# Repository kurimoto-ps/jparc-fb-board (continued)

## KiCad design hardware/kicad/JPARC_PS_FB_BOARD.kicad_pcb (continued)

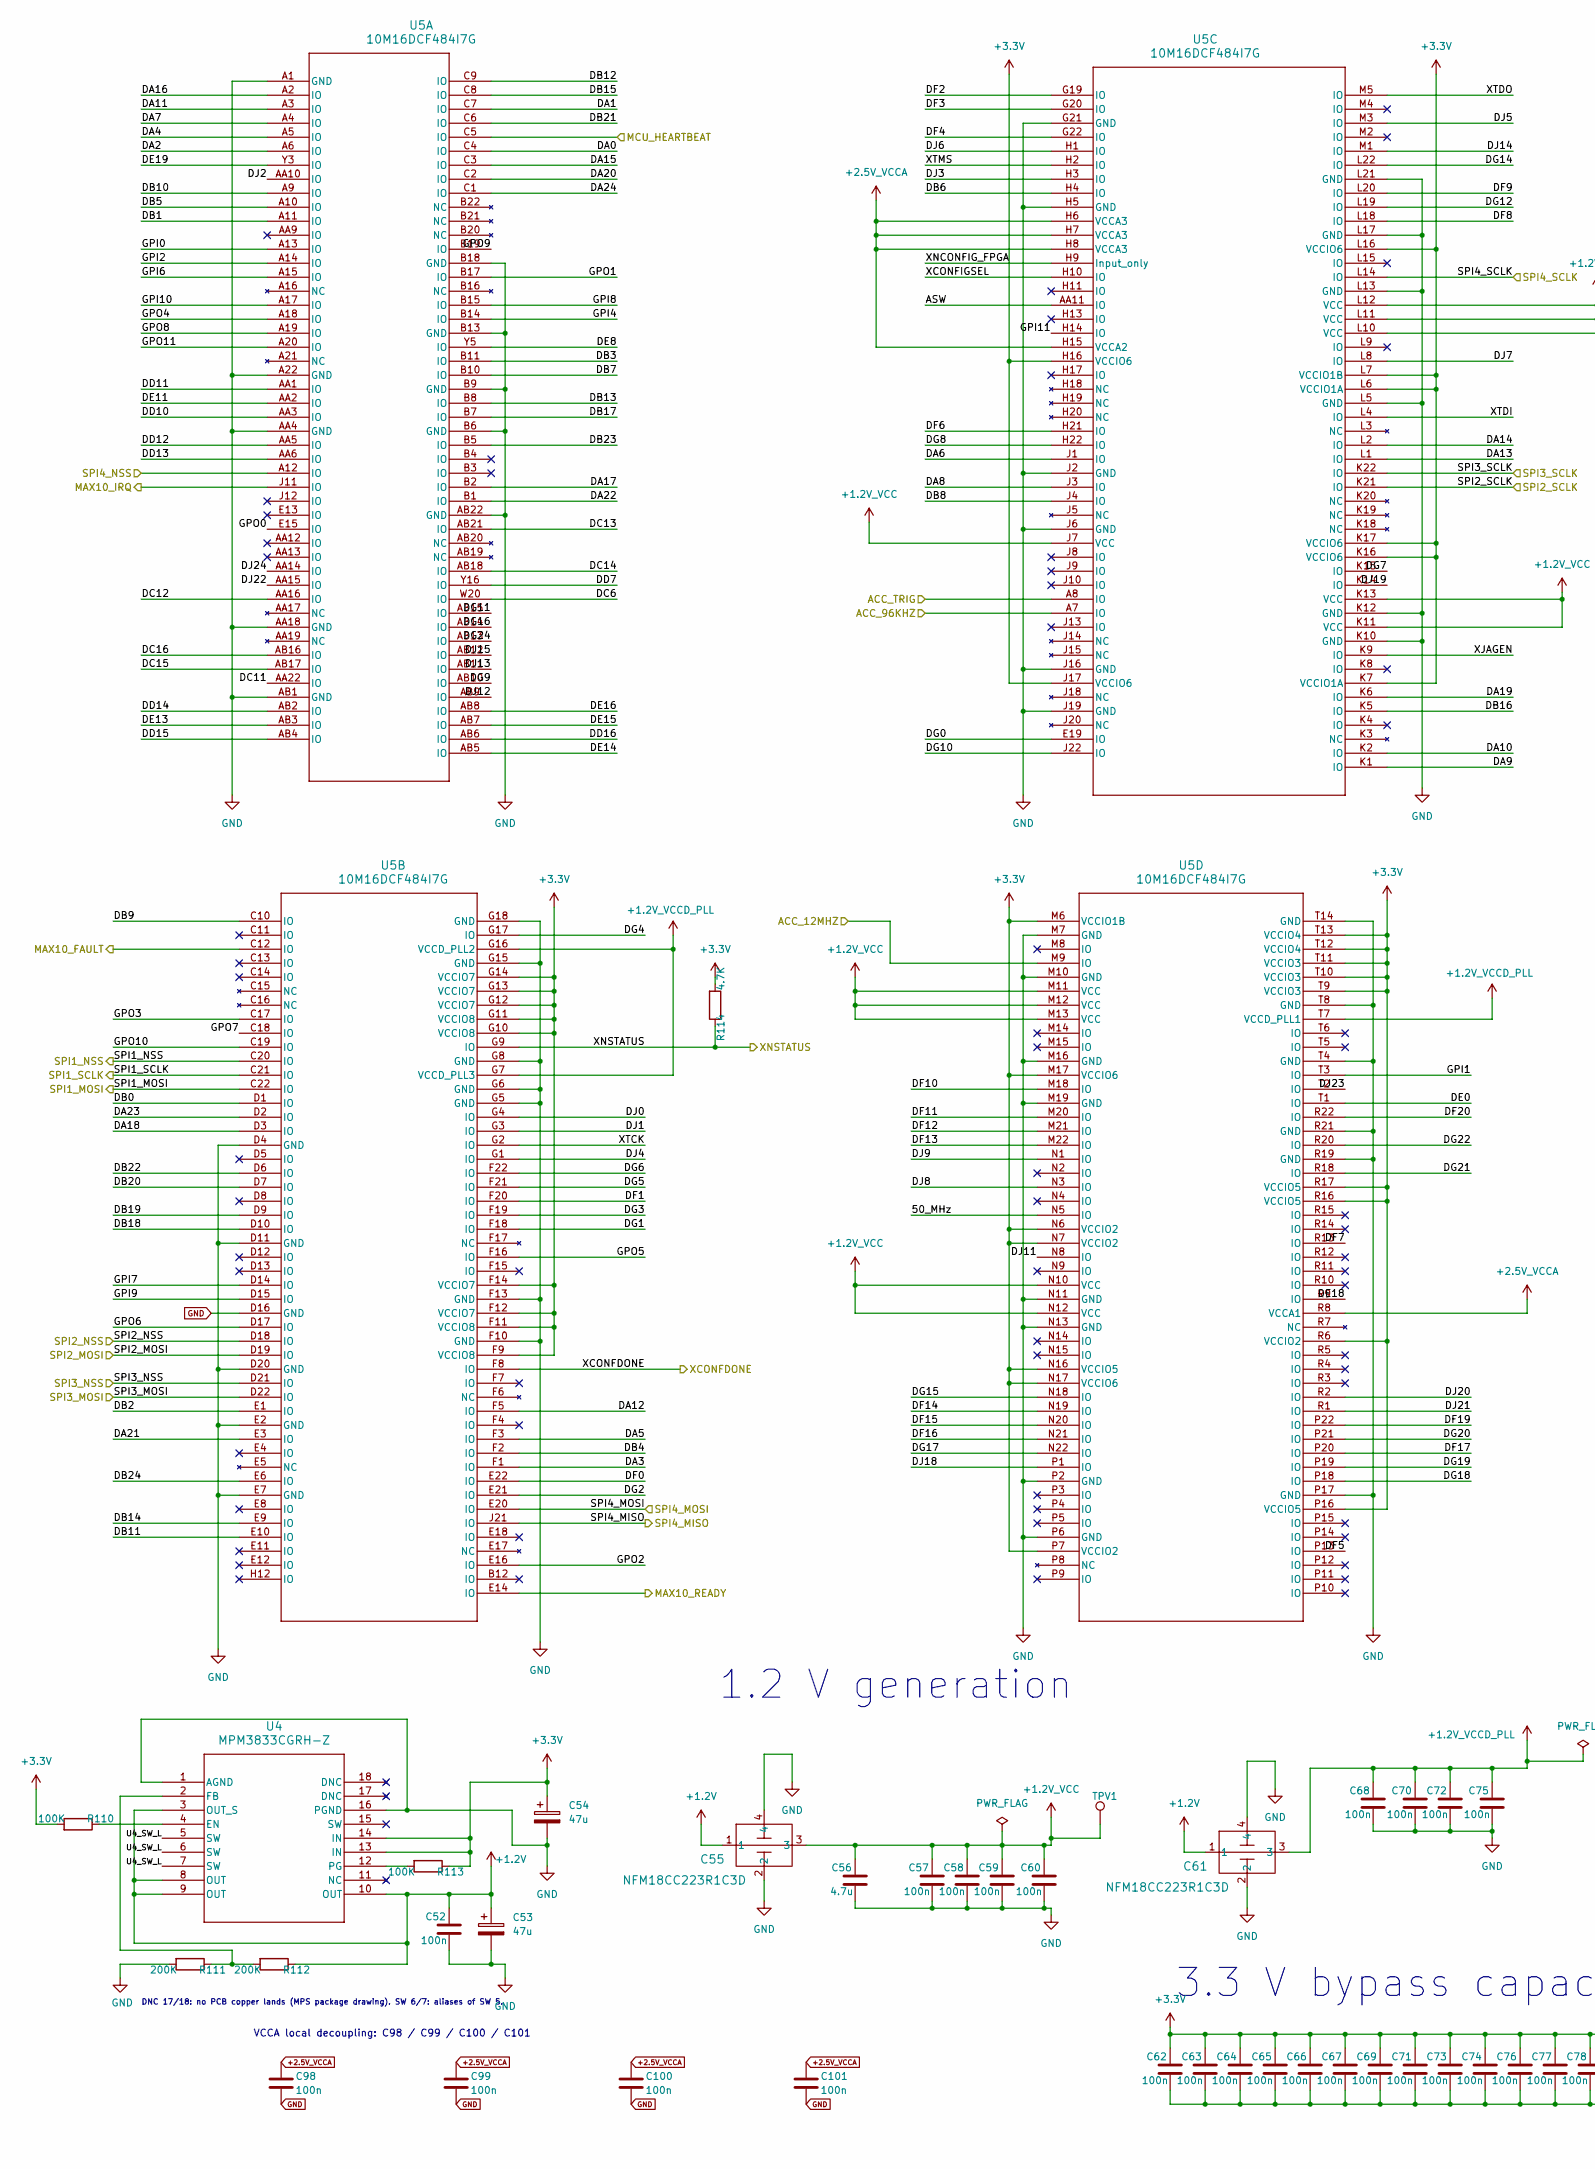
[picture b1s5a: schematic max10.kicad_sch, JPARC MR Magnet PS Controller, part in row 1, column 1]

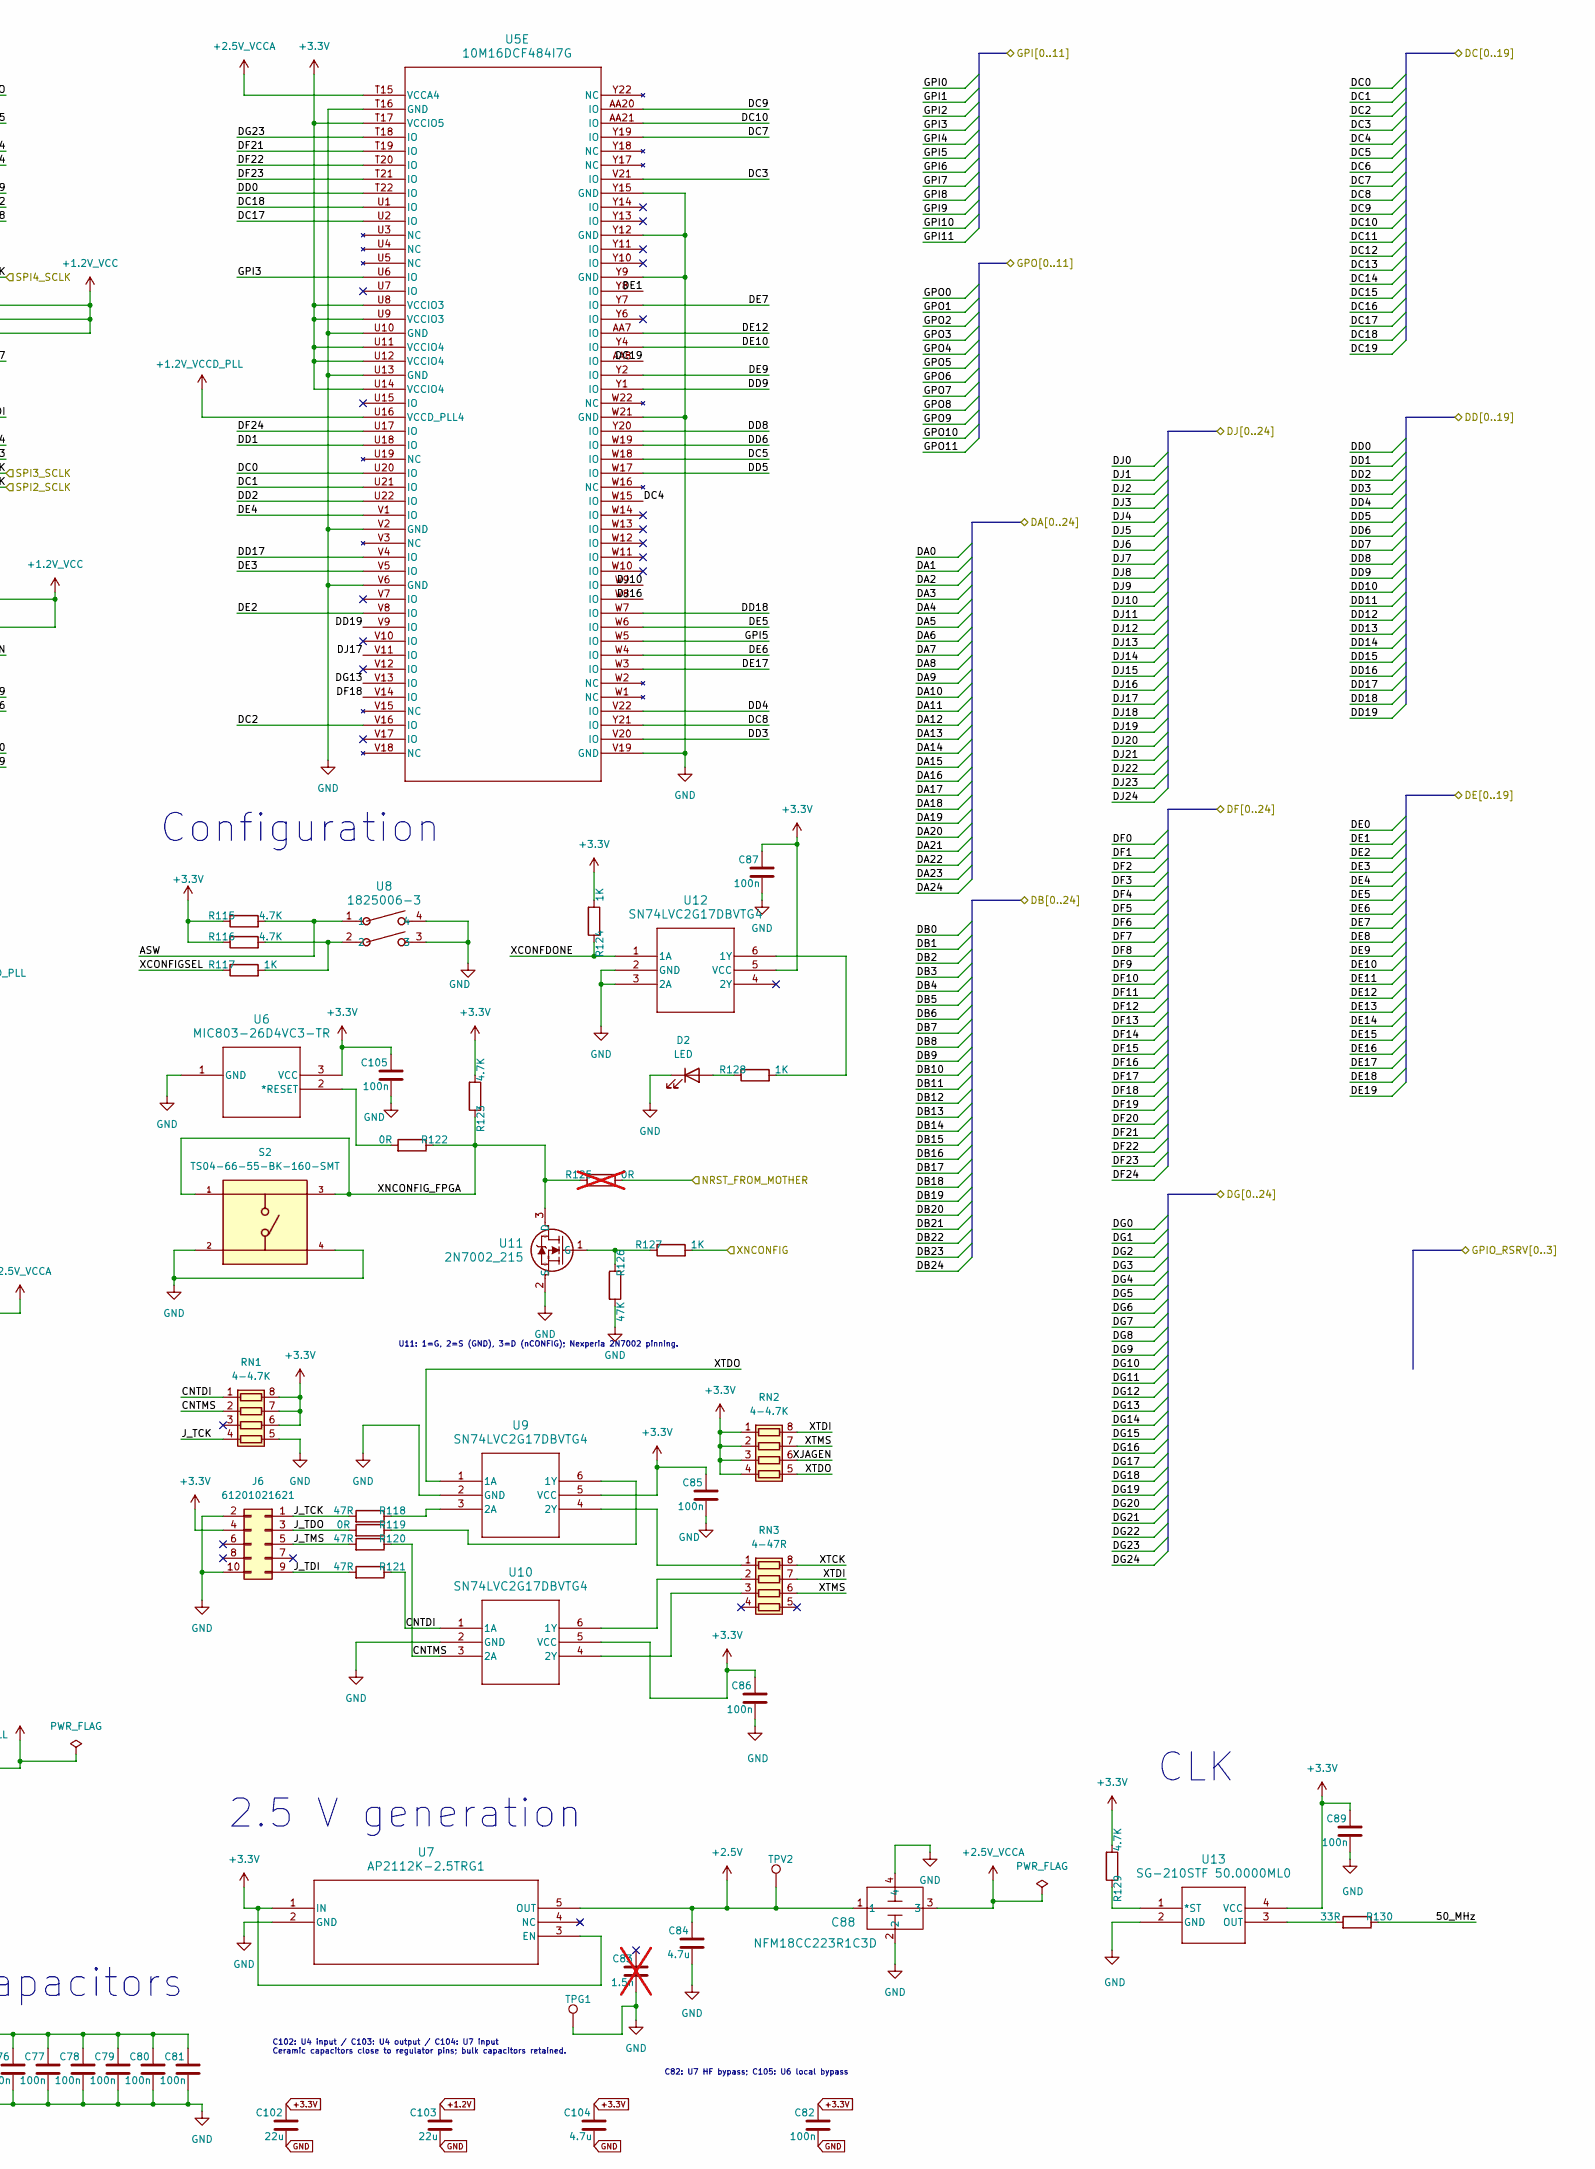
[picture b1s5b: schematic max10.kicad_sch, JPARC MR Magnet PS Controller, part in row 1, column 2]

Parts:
C52, C57, C58, C59, C60, C62, C63, C64, C65, C66, C67, C68, C69, C70, C71, C72, C73, C74, C75, C76, C77, C78, C79, C80, C81, C82, C85, C86, C87, C89, C98, C99, C100, C101, C105: 100n; C_0402_1005Metric
C53, C54: 47u; CP_Elec_5x5.8
C55, C61, C88: NFM18CC223R1C3D; NFM18CC_4Pad_Corrected
C56, C84, C104: 4.7u; C_0805_2012Metric
C83: 1.5n; C_0603_1608Metric; not fitted
C102, C103: 22u; C_0805_2012Metric
D2: LED; LED_0805_2012Metric
J6: 61201021621; IDC-Header_2x05_P2.54mm_Vertical
R110, R113: 100K; R_0603_1608Metric
R111, R112: 200K; R_0603_1608Metric
R114, R115, R116, R123, R129: 4.7K; R_0603_1608Metric
R117, R124, R127, R128: 1K; R_0603_1608Metric
R118, R120, R121: 47R; R_0402_1005Metric
R119, R122: 0R; R_0603_1608Metric
R125: 0R; R_0603_1608Metric; not fitted
R126: 47K; R_0603_1608Metric
R130: 33R; R_0402_1005Metric
RN1, RN2: 4-4.7K; R_Cat16-4
RN3: 4-47R; R_Cat16-4
S2: TS04-66-55-BK-160-SMT; SW_TS04-66-55-BK-160-SMT; PARTREV 1.0
TPG1: TestPoint_THTPad_D1.0mm_Drill0.5mm
TPV1, TPV2: TestPoint_Pad_D1.5mm
U4: MPM3833CGRH-Z; MPM3833C_QFN18_Manufacturer
U5: 10M16DCF484I7G; FBGA484_WIREBOND_A2p40_INT
U6: MIC803-26D4VC3-TR; 21-0075D_MXM
U7: AP2112K-2.5TRG1; UJ_5_ADI
U8: 1825006-3; SWSO4_386X100P100
U9, U10, U12: SN74LVC2G17DBVTG4; DBV6_TEX
U11: 2N7002_215; TO-236AB_NEX
U13: SG-210STF 50.0000ML0; SG-210STF_Epson_Recommended

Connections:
+1.2V: C52.1, C53.1, C55.1, C61.1, C103.1, R112.1, U4.3 (OUT_S), U4.8 (OUT), U4.9 (OUT), U4.10 (OUT)
+1.2V_VCC: C55.3, C56.1, C57.1, C58.1, C59.1, C60.1, TPV1.1 (1_1), U5.J7 (VCC), U5.K11 (VCC), U5.K13 (VCC), U5.L10 (VCC), U5.L11 (VCC), U5.L12 (VCC), U5.M11 (VCC), U5.M12 (VCC), U5.M13 (VCC), U5.N10 (VCC), U5.N12 (VCC)
+1.2V_VCCD_PLL: C61.3, C68.1, C70.1, C72.1, C75.1, U5.G7 (VCCD_PLL3), U5.G16 (VCCD_PLL2), U5.T7 (VCCD_PLL1), U5.U16 (VCCD_PLL4)
+2.5V: C84.1, C88.1, TPV2.1 (1_1), U7.5 (OUT)
+2.5V_VCCA: C88.3, C98.1, C99.1, C100.1, C101.1, U5.H6 (VCCA3), U5.H7 (VCCA3), U5.H8 (VCCA3), U5.H15 (VCCA2), U5.R8 (VCCA1), U5.T15 (VCCA4)
+3.3V: C54.1, C62.1, C63.1, C64.1, C65.1, C66.1, C67.1, C69.1, C71.1, C73.1, C74.1, C76.1, C77.1, C78.1, C79.1, C80.1, C81.1, C82.1, C85.1, C86.1, C87.1, C89.1, C102.1, C104.1, C105.1, J6.4, R110.2, R113.1, R114.2, R115.1, R116.1, R123.2, R124.2, R129.2, RN1.6 (R3.2), RN1.7 (R2.2), RN1.8 (R1.2), RN2.1 (R1.1), RN2.2 (R2.1), RN2.3 (R3.1), RN2.4 (R4.1), U4.13 (IN), U4.14 (IN), U5.F9 (VCCIO8), U5.F11 (VCCIO8), U5.F12 (VCCIO7), U5.F14 (VCCIO7), U5.G10 (VCCIO8), U5.G11 (VCCIO8), U5.G12 (VCCIO7), U5.G13 (VCCIO7), U5.G14 (VCCIO7), U5.H16 (VCCIO6), U5.J17 (VCCIO6), U5.K7 (VCCIO1A), U5.K16 (VCCIO6), U5.K17 (VCCIO6), U5.L6 (VCCIO1A), U5.L7 (VCCIO1B), U5.L16 (VCCIO6), U5.M6 (VCCIO1B), U5.M17 (VCCIO6), U5.N6 (VCCIO2), U5.N7 (VCCIO2), U5.N16 (VCCIO5), U5.N17 (VCCIO6), U5.P7 (VCCIO2), U5.P16 (VCCIO5), U5.R6 (VCCIO2), U5.R16 (VCCIO5), U5.R17 (VCCIO5), U5.T9 (VCCIO3), U5.T10 (VCCIO3), U5.T11 (VCCIO3), U5.T12 (VCCIO4), U5.T13 (VCCIO4), U5.T17 (VCCIO5), U5.U8 (VCCIO3), U5.U9 (VCCIO3), U5.U11 (VCCIO4), U5.U12 (VCCIO4), U5.U14 (VCCIO4), U6.3 (VCC), U7.1 (IN), U7.3 (EN), U9.5 (VCC), U10.5 (VCC), U12.5 (VCC), U13.4 (VCC); also elsewhere on the board
/Interface Sheet/ACC_12MHZ: U5.M9 (IO); also elsewhere on the board
/Interface Sheet/ACC_TRIG: U5.A8 (IO); also elsewhere on the board
/Interface Sheet/DA0: U5.C4 (IO); also elsewhere on the board
/Interface Sheet/DA1: U5.C7 (IO); also elsewhere on the board
/Interface Sheet/DA2: U5.A6 (IO); also elsewhere on the board
/Interface Sheet/DA3: U5.F1 (IO); also elsewhere on the board
/Interface Sheet/DA4: U5.A5 (IO); also elsewhere on the board
/Interface Sheet/DA5: U5.F3 (IO); also elsewhere on the board
/Interface Sheet/DA6: U5.J1 (IO); also elsewhere on the board
/Interface Sheet/DA7: U5.A4 (IO); also elsewhere on the board
/Interface Sheet/DA8: U5.J3 (IO); also elsewhere on the board
/Interface Sheet/DA9: U5.K1 (IO); also elsewhere on the board
/Interface Sheet/DA10: U5.K2 (IO); also elsewhere on the board
/Interface Sheet/DA11: U5.A3 (IO); also elsewhere on the board
/Interface Sheet/DA12: U5.F5 (IO); also elsewhere on the board
/Interface Sheet/DA13: U5.L1 (IO); also elsewhere on the board
/Interface Sheet/DA14: U5.L2 (IO); also elsewhere on the board
/Interface Sheet/DA15: U5.C3 (IO); also elsewhere on the board
/Interface Sheet/DA16: U5.A2 (IO); also elsewhere on the board
/Interface Sheet/DA17: U5.B2 (IO); also elsewhere on the board
/Interface Sheet/DA18: U5.D3 (IO); also elsewhere on the board
/Interface Sheet/DA19: U5.K6 (IO); also elsewhere on the board
/Interface Sheet/DA20: U5.C2 (IO); also elsewhere on the board
/Interface Sheet/DA21: U5.E3 (IO); also elsewhere on the board
/Interface Sheet/DA22: U5.B1 (IO); also elsewhere on the board
/Interface Sheet/DA23: U5.D2 (IO); also elsewhere on the board
/Interface Sheet/DA24: U5.C1 (IO); also elsewhere on the board
/Interface Sheet/DB0: U5.D1 (IO); also elsewhere on the board
/Interface Sheet/DB1: U5.A11 (IO); also elsewhere on the board
/Interface Sheet/DB2: U5.E1 (IO); also elsewhere on the board
/Interface Sheet/DB3: U5.B11 (IO); also elsewhere on the board
/Interface Sheet/DB4: U5.F2 (IO); also elsewhere on the board
/Interface Sheet/DB5: U5.A10 (IO); also elsewhere on the board
/Interface Sheet/DB6: U5.H4 (IO); also elsewhere on the board
/Interface Sheet/DB7: U5.B10 (IO); also elsewhere on the board
/Interface Sheet/DB8: U5.J4 (IO); also elsewhere on the board
/Interface Sheet/DB9: U5.C10 (IO); also elsewhere on the board
/Interface Sheet/DB10: U5.A9 (IO); also elsewhere on the board
/Interface Sheet/DB11: U5.E10 (IO); also elsewhere on the board
/Interface Sheet/DB12: U5.C9 (IO); also elsewhere on the board
/Interface Sheet/DB13: U5.B8 (IO); also elsewhere on the board
/Interface Sheet/DB14: U5.E9 (IO); also elsewhere on the board
/Interface Sheet/DB15: U5.C8 (IO); also elsewhere on the board
/Interface Sheet/DB16: U5.K5 (IO); also elsewhere on the board
/Interface Sheet/DB17: U5.B7 (IO); also elsewhere on the board
/Interface Sheet/DB18: U5.D10 (IO); also elsewhere on the board
/Interface Sheet/DB19: U5.D9 (IO); also elsewhere on the board
/Interface Sheet/DB20: U5.D7 (IO); also elsewhere on the board
/Interface Sheet/DB21: U5.C6 (IO); also elsewhere on the board
/Interface Sheet/DB22: U5.D6 (IO); also elsewhere on the board
/Interface Sheet/DB23: U5.B5 (IO); also elsewhere on the board
/Interface Sheet/DB24: U5.E6 (IO); also elsewhere on the board
/Interface Sheet/DC0: U5.U20 (IO); also elsewhere on the board
/Interface Sheet/DC1: U5.U21 (IO); also elsewhere on the board
/Interface Sheet/DC2: U5.V16 (IO); also elsewhere on the board
/Interface Sheet/DC3: U5.V21 (IO); also elsewhere on the board
/Interface Sheet/DC4: U5.W15 (IO); also elsewhere on the board
/Interface Sheet/DC5: U5.W18 (IO); also elsewhere on the board
/Interface Sheet/DC6: U5.W20 (IO); also elsewhere on the board
/Interface Sheet/DC7: U5.Y19 (IO); also elsewhere on the board
/Interface Sheet/DC8: U5.Y21 (IO); also elsewhere on the board
/Interface Sheet/DC9: U5.AA20 (IO); also elsewhere on the board
/Interface Sheet/DC10: U5.AA21 (IO); also elsewhere on the board
/Interface Sheet/DC11: U5.AA22 (IO); also elsewhere on the board
/Interface Sheet/DC12: U5.AA16 (IO); also elsewhere on the board
/Interface Sheet/DC13: U5.AB21 (IO); also elsewhere on the board
/Interface Sheet/DC14: U5.AB18 (IO); also elsewhere on the board
/Interface Sheet/DC15: U5.AB17 (IO); also elsewhere on the board
/Interface Sheet/DC16: U5.AB16 (IO); also elsewhere on the board
/Interface Sheet/DC17: U5.U2 (IO); also elsewhere on the board
/Interface Sheet/DC18: U5.U1 (IO); also elsewhere on the board
/Interface Sheet/DC19: U5.AA8 (IO); also elsewhere on the board
/Interface Sheet/DD0: U5.T22 (IO); also elsewhere on the board
/Interface Sheet/DD1: U5.U18 (IO); also elsewhere on the board
/Interface Sheet/DD2: U5.U22 (IO); also elsewhere on the board
/Interface Sheet/DD3: U5.V20 (IO); also elsewhere on the board
/Interface Sheet/DD4: U5.V22 (IO); also elsewhere on the board
/Interface Sheet/DD5: U5.W17 (IO); also elsewhere on the board
/Interface Sheet/DD6: U5.W19 (IO); also elsewhere on the board
/Interface Sheet/DD7: U5.Y16 (IO); also elsewhere on the board
/Interface Sheet/DD8: U5.Y20 (IO); also elsewhere on the board
/Interface Sheet/DD9: U5.Y1 (IO); also elsewhere on the board
/Interface Sheet/DD10: U5.AA3 (IO); also elsewhere on the board
/Interface Sheet/DD11: U5.AA1 (IO); also elsewhere on the board
/Interface Sheet/DD12: U5.AA5 (IO); also elsewhere on the board
/Interface Sheet/DD13: U5.AA6 (IO); also elsewhere on the board
/Interface Sheet/DD14: U5.AB2 (IO); also elsewhere on the board
/Interface Sheet/DD15: U5.AB4 (IO); also elsewhere on the board
/Interface Sheet/DD16: U5.AB6 (IO); also elsewhere on the board
/Interface Sheet/DD17: U5.V4 (IO); also elsewhere on the board
/Interface Sheet/DD18: U5.W7 (IO); also elsewhere on the board
/Interface Sheet/DD19: U5.V9 (IO); also elsewhere on the board
/Interface Sheet/DE0: U5.T1 (IO); also elsewhere on the board
/Interface Sheet/DE1: U5.Y8 (IO); also elsewhere on the board
/Interface Sheet/DE2: U5.V8 (IO); also elsewhere on the board
/Interface Sheet/DE3: U5.V5 (IO); also elsewhere on the board
/Interface Sheet/DE4: U5.V1 (IO); also elsewhere on the board
/Interface Sheet/DE5: U5.W6 (IO); also elsewhere on the board
/Interface Sheet/DE6: U5.W4 (IO); also elsewhere on the board
/Interface Sheet/DE7: U5.Y7 (IO); also elsewhere on the board
/Interface Sheet/DE8: U5.Y5 (IO); also elsewhere on the board
/Interface Sheet/DE9: U5.Y2 (IO); also elsewhere on the board
/Interface Sheet/DE10: U5.Y4 (IO); also elsewhere on the board
/Interface Sheet/DE11: U5.AA2 (IO); also elsewhere on the board
/Interface Sheet/DE12: U5.AA7 (IO); also elsewhere on the board
/Interface Sheet/DE13: U5.AB3 (IO); also elsewhere on the board
/Interface Sheet/DE14: U5.AB5 (IO); also elsewhere on the board
/Interface Sheet/DE15: U5.AB7 (IO); also elsewhere on the board
/Interface Sheet/DE16: U5.AB8 (IO); also elsewhere on the board
/Interface Sheet/DE17: U5.W3 (IO); also elsewhere on the board
/Interface Sheet/DE18: U5.R9 (IO); also elsewhere on the board
/Interface Sheet/DE19: U5.Y3 (IO); also elsewhere on the board
/Interface Sheet/DF0: U5.E22 (IO); also elsewhere on the board
/Interface Sheet/DF1: U5.F20 (IO); also elsewhere on the board
/Interface Sheet/DF2: U5.G19 (IO); also elsewhere on the board
/Interface Sheet/DF3: U5.G20 (IO); also elsewhere on the board
/Interface Sheet/DF4: U5.G22 (IO); also elsewhere on the board
/Interface Sheet/DF5: U5.P13 (IO); also elsewhere on the board
/Interface Sheet/DF6: U5.H21 (IO); also elsewhere on the board
/Interface Sheet/DF7: U5.R13 (IO); also elsewhere on the board
/Interface Sheet/DF8: U5.L18 (IO); also elsewhere on the board
/Interface Sheet/DF9: U5.L20 (IO); also elsewhere on the board
/Interface Sheet/DF10: U5.M18 (IO); also elsewhere on the board
/Interface Sheet/DF11: U5.M20 (IO); also elsewhere on the board
/Interface Sheet/DF12: U5.M21 (IO); also elsewhere on the board
/Interface Sheet/DF13: U5.M22 (IO); also elsewhere on the board
/Interface Sheet/DF14: U5.N19 (IO); also elsewhere on the board
/Interface Sheet/DF15: U5.N20 (IO); also elsewhere on the board
/Interface Sheet/DF16: U5.N21 (IO); also elsewhere on the board
/Interface Sheet/DF17: U5.P20 (IO); also elsewhere on the board
/Interface Sheet/DF18: U5.V14 (IO); also elsewhere on the board
/Interface Sheet/DF19: U5.P22 (IO); also elsewhere on the board
/Interface Sheet/DF20: U5.R22 (IO); also elsewhere on the board
/Interface Sheet/DF21: U5.T19 (IO); also elsewhere on the board
/Interface Sheet/DF22: U5.T20 (IO); also elsewhere on the board
/Interface Sheet/DF23: U5.T21 (IO); also elsewhere on the board
/Interface Sheet/DF24: U5.U17 (IO); also elsewhere on the board
/Interface Sheet/DG0: U5.E19 (IO); also elsewhere on the board
/Interface Sheet/DG1: U5.F18 (IO); also elsewhere on the board
/Interface Sheet/DG2: U5.E21 (IO); also elsewhere on the board
/Interface Sheet/DG3: U5.F19 (IO); also elsewhere on the board
/Interface Sheet/DG4: U5.G17 (IO); also elsewhere on the board
/Interface Sheet/DG5: U5.F21 (IO); also elsewhere on the board
/Interface Sheet/DG6: U5.F22 (IO); also elsewhere on the board
/Interface Sheet/DG7: U5.K15 (IO); also elsewhere on the board
/Interface Sheet/DG8: U5.H22 (IO); also elsewhere on the board
/Interface Sheet/DG9: U5.AB10 (IO); also elsewhere on the board
/Interface Sheet/DG10: U5.J22 (IO); also elsewhere on the board
/Interface Sheet/DG11: U5.AB15 (IO); also elsewhere on the board
/Interface Sheet/DG12: U5.L19 (IO); also elsewhere on the board
/Interface Sheet/DG13: U5.V13 (IO); also elsewhere on the board
/Interface Sheet/DG14: U5.L22 (IO); also elsewhere on the board
/Interface Sheet/DG15: U5.N18 (IO); also elsewhere on the board
/Interface Sheet/DG16: U5.AB14 (IO); also elsewhere on the board
/Interface Sheet/DG17: U5.N22 (IO); also elsewhere on the board
/Interface Sheet/DG18: U5.P18 (IO); also elsewhere on the board
/Interface Sheet/DG19: U5.P19 (IO); also elsewhere on the board
/Interface Sheet/DG20: U5.P21 (IO); also elsewhere on the board
/Interface Sheet/DG21: U5.R18 (IO); also elsewhere on the board
/Interface Sheet/DG22: U5.R20 (IO); also elsewhere on the board
/Interface Sheet/DG23: U5.T18 (IO); also elsewhere on the board
/Interface Sheet/DG24: U5.AB13 (IO); also elsewhere on the board
/Interface Sheet/DJ0: U5.G4 (IO); also elsewhere on the board
/Interface Sheet/DJ1: U5.G3 (IO); also elsewhere on the board
/Interface Sheet/DJ2: U5.AA10 (IO); also elsewhere on the board
/Interface Sheet/DJ3: U5.H3 (IO); also elsewhere on the board
/Interface Sheet/DJ4: U5.G1 (IO); also elsewhere on the board
/Interface Sheet/DJ5: U5.M3 (IO); also elsewhere on the board
/Interface Sheet/DJ6: U5.H1 (IO); also elsewhere on the board
/Interface Sheet/DJ7: U5.L8 (IO); also elsewhere on the board
/Interface Sheet/DJ8: U5.N3 (IO); also elsewhere on the board
/Interface Sheet/DJ9: U5.N1 (IO); also elsewhere on the board
/Interface Sheet/DJ10: U5.W9 (IO); also elsewhere on the board
/Interface Sheet/DJ11: U5.N8 (IO); also elsewhere on the board
/Interface Sheet/DJ12: U5.AB9 (IO); also elsewhere on the board
/Interface Sheet/DJ13: U5.AB11 (IO); also elsewhere on the board
/Interface Sheet/DJ14: U5.M1 (IO); also elsewhere on the board
/Interface Sheet/DJ15: U5.AB12 (IO); also elsewhere on the board
/Interface Sheet/DJ16: U5.W8 (IO); also elsewhere on the board
/Interface Sheet/DJ17: U5.V11 (IO); also elsewhere on the board
/Interface Sheet/DJ18: U5.P1 (IO); also elsewhere on the board
/Interface Sheet/DJ19: U5.K14 (IO); also elsewhere on the board
/Interface Sheet/DJ20: U5.R2 (IO); also elsewhere on the board
/Interface Sheet/DJ21: U5.R1 (IO); also elsewhere on the board
/Interface Sheet/DJ22: U5.AA15 (IO); also elsewhere on the board
/Interface Sheet/DJ23: U5.T2 (IO); also elsewhere on the board
/Interface Sheet/DJ24: U5.AA14 (IO); also elsewhere on the board
/Interface Sheet/GPI0: U5.A13 (IO); also elsewhere on the board
/Interface Sheet/GPI1: U5.T3 (IO); also elsewhere on the board
/Interface Sheet/GPI2: U5.A14 (IO); also elsewhere on the board
/Interface Sheet/GPI3: U5.U6 (IO); also elsewhere on the board
/Interface Sheet/GPI4: U5.B14 (IO); also elsewhere on the board
/Interface Sheet/GPI5: U5.W5 (IO); also elsewhere on the board
/Interface Sheet/GPI6: U5.A15 (IO); also elsewhere on the board
/Interface Sheet/GPI7: U5.D14 (IO); also elsewhere on the board
/Interface Sheet/GPI8: U5.B15 (IO); also elsewhere on the board
/Interface Sheet/GPI9: U5.D15 (IO); also elsewhere on the board
/Interface Sheet/GPI10: U5.A17 (IO); also elsewhere on the board
/Interface Sheet/GPI11: U5.H14 (IO); also elsewhere on the board
/Interface Sheet/GPO0: U5.E15 (IO); also elsewhere on the board
/Interface Sheet/GPO1: U5.B17 (IO); also elsewhere on the board
/Interface Sheet/GPO2: U5.E16 (IO); also elsewhere on the board
/Interface Sheet/GPO3: U5.C17 (IO); also elsewhere on the board
/Interface Sheet/GPO4: U5.A18 (IO); also elsewhere on the board
/Interface Sheet/GPO5: U5.F16 (IO); also elsewhere on the board
/Interface Sheet/GPO6: U5.D17 (IO); also elsewhere on the board
/Interface Sheet/GPO7: U5.C18 (IO); also elsewhere on the board
/Interface Sheet/GPO8: U5.A19 (IO); also elsewhere on the board
/Interface Sheet/GPO9: U5.B19 (IO); also elsewhere on the board
/Interface Sheet/GPO10: U5.C19 (IO); also elsewhere on the board
/Interface Sheet/GPO11: U5.A20 (IO); also elsewhere on the board
/Interface Sheet/RESET: R125.2; also elsewhere on the board
/MAX10 Sheet/50_MHz: R130.1, U5.N5 (IO)
/MAX10 Sheet/ASW: R115.2, U5.AA11 (IO), U8.1
/MAX10 Sheet/CNTDI: R121.1, RN1.1 (R1.1), U10.1 (1A)
/MAX10 Sheet/CNTMS: R120.1, RN1.2 (R2.1), U10.3 (2A)
/MAX10 Sheet/J_TCK: J6.1, R118.2, RN1.4 (R4.1)
/MAX10 Sheet/J_TDI: J6.9, R121.2
/MAX10 Sheet/J_TDO: J6.3, R119.2
/MAX10 Sheet/J_TMS: J6.5, R120.2
/MAX10 Sheet/MAX10_FAULT: U5.C12 (IO); also elsewhere on the board
/MAX10 Sheet/MAX10_IRQ: U5.J11 (IO); also elsewhere on the board
/MAX10 Sheet/MAX10_READY: U5.E14 (IO); also elsewhere on the board
/MAX10 Sheet/MCU_HEARTBEAT: U5.C5 (IO); also elsewhere on the board
/MAX10 Sheet/SPI1_MOSI: U5.C22 (IO); also elsewhere on the board
/MAX10 Sheet/SPI1_NSS: U5.C20 (IO); also elsewhere on the board
/MAX10 Sheet/SPI1_SCLK: U5.C21 (IO); also elsewhere on the board
/MAX10 Sheet/SPI2_MOSI: U5.D19 (IO); also elsewhere on the board
/MAX10 Sheet/SPI2_NSS: U5.D18 (IO); also elsewhere on the board
/MAX10 Sheet/SPI2_SCLK: U5.K21 (IO); also elsewhere on the board
/MAX10 Sheet/SPI3_MOSI: U5.D22 (IO); also elsewhere on the board
/MAX10 Sheet/SPI3_NSS: U5.D21 (IO); also elsewhere on the board
/MAX10 Sheet/SPI3_SCLK: U5.K22 (IO); also elsewhere on the board
/MAX10 Sheet/SPI4_MISO: U5.J21 (IO); also elsewhere on the board
/MAX10 Sheet/SPI4_MOSI: U5.E20 (IO); also elsewhere on the board
/MAX10 Sheet/SPI4_NSS: U5.A12 (IO); also elsewhere on the board
/MAX10 Sheet/SPI4_SCLK: U5.L14 (IO); also elsewhere on the board
/MAX10 Sheet/U4_SW_L: U4.5 (SW), U4.6 (SW), U4.7 (SW)
/MAX10 Sheet/XCONFDONE: R124.1, U5.F8 (IO), U12.1 (1A); also elsewhere on the board
/MAX10 Sheet/XCONFIGSEL: R117.1, U5.H10 (IO)
/MAX10 Sheet/XJAGEN: RN2.6 (R3.2), U5.K9 (IO)
/MAX10 Sheet/XNCONFIG: R127.2; also elsewhere on the board
/MAX10 Sheet/XNCONFIG_FPGA: R122.1, R123.1, R125.1, S2.1, S2.3, U5.H9 (Input_only), U11.3
/MAX10 Sheet/XNSTATUS: R114.1, U5.G9 (IO); also elsewhere on the board
/MAX10 Sheet/XTCK: RN3.8 (R1.2), U5.G2 (IO)
/MAX10 Sheet/XTDI: RN2.8 (R1.2), RN3.7 (R2.2), U5.L4 (IO)
/MAX10 Sheet/XTDO: RN2.5 (R4.2), U5.M5 (IO), U9.1 (1A)
/MAX10 Sheet/XTMS: RN2.7 (R2.2), RN3.6 (R3.2), U5.H2 (IO)
/STM32H7 Sheet/PA0: U5.A7 (IO); also elsewhere on the board
GND: C52.2, C53.2, C54.2, C55.2, C55.4, C56.2, C57.2, C58.2, C59.2, C60.2, C61.2, C61.4, C62.2, C63.2, C64.2, C65.2, C66.2, C67.2, C68.2, C69.2, C70.2, C71.2, C72.2, C73.2, C74.2, C75.2, C76.2, C77.2, C78.2, C79.2, C80.2, C81.2, C82.2, C83.2, C84.2, C85.2, C86.2, C87.2, C88.2, C88.4, C89.2, C98.2, C99.2, C100.2, C101.2, C102.2, C103.2, C104.2, C105.2, D2.1 (K), J6.2, J6.10, R111.2, R126.2, RN1.5 (R4.2), S2.2, S2.4, TPG1.1 (1_1), U4.1 (AGND), U4.16 (PGND), U5.A1 (GND), U5.A22 (GND), U5.AA4 (GND), U5.AA18 (GND), U5.AB1 (GND), U5.AB22 (GND), U5.B6 (GND), U5.B9 (GND), U5.B13 (GND), U5.B18 (GND), U5.D4 (GND), U5.D11 (GND), U5.D16 (GND), U5.D20 (GND), U5.E2 (GND), U5.E7 (GND), U5.F10 (GND), U5.F13 (GND), U5.G5 (GND), U5.G6 (GND), U5.G8 (GND), U5.G15 (GND), U5.G18 (GND), U5.G21 (GND), U5.H5 (GND), U5.J2 (GND), U5.J6 (GND), U5.J16 (GND), U5.J19 (GND), U5.K10 (GND), U5.K12 (GND), U5.L5 (GND), U5.L13 (GND), U5.L17 (GND), U5.L21 (GND), U5.M7 (GND), U5.M10 (GND), U5.M16 (GND), U5.M19 (GND), U5.N11 (GND), U5.N13 (GND), U5.P2 (GND), U5.P6 (GND), U5.P17 (GND), U5.R19 (GND), U5.R21 (GND), U5.T4 (GND), U5.T8 (GND), U5.T14 (GND), U5.T16 (GND), U5.U10 (GND), U5.U13 (GND), U5.V2 (GND), U5.V6 (GND), U5.V19 (GND), U5.W21 (GND), U5.Y9 (GND), U5.Y12 (GND), U5.Y15 (GND), U6.1 (GND), U7.2 (GND), U8.3, U8.4, U9.2 (GND), U10.2 (GND), U11.2, U12.2 (GND), U12.3 (2A), U13.2 (GND); also elsewhere on the board
unnamed: D2.2 (A), R128.1
unnamed: R116.2, R117.2, U8.2
unnamed: RN3.1 (R1.1), U9.4 (2Y)
unnamed: RN3.2 (R2.1), U10.6 (1Y)
unnamed: RN3.3 (R3.1), U10.4 (2Y)
unnamed: R110.1, U4.4 (EN)
unnamed: R111.1, R112.2, U4.2 (FB)
unnamed: R113.2, U4.12 (PG)
unnamed: R122.2, U6.2 (*RESET)
unnamed: R119.1, U9.6 (1Y)
unnamed: R118.1, U9.3 (2A)
unnamed: R126.1, R127.1, U11.1
unnamed: R128.2, U12.6 (1Y)
unnamed: R129.1, U13.1 (*ST)
unnamed: R130.2, U13.3 (OUT)

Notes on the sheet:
3.3 V bypass capacitors
1.2 V generation
Configuration
CLK
2.5 V generation
VCCA local decoupling: C98 / C99 / C100 / C101
C102: U4 input / C103: U4 output / C104: U7 input Ceramic capacitors close to regulator pins; bulk capacitors retained.
DNC 17/18: no PCB copper lands (MPS package drawing). SW 6/7: aliases of SW 5.
C82: U7 HF bypass; C105: U6 local bypass
U11: 1=G, 2=S (GND), 3=D (nCONFIG); Nexperia 2N7002 pinning.

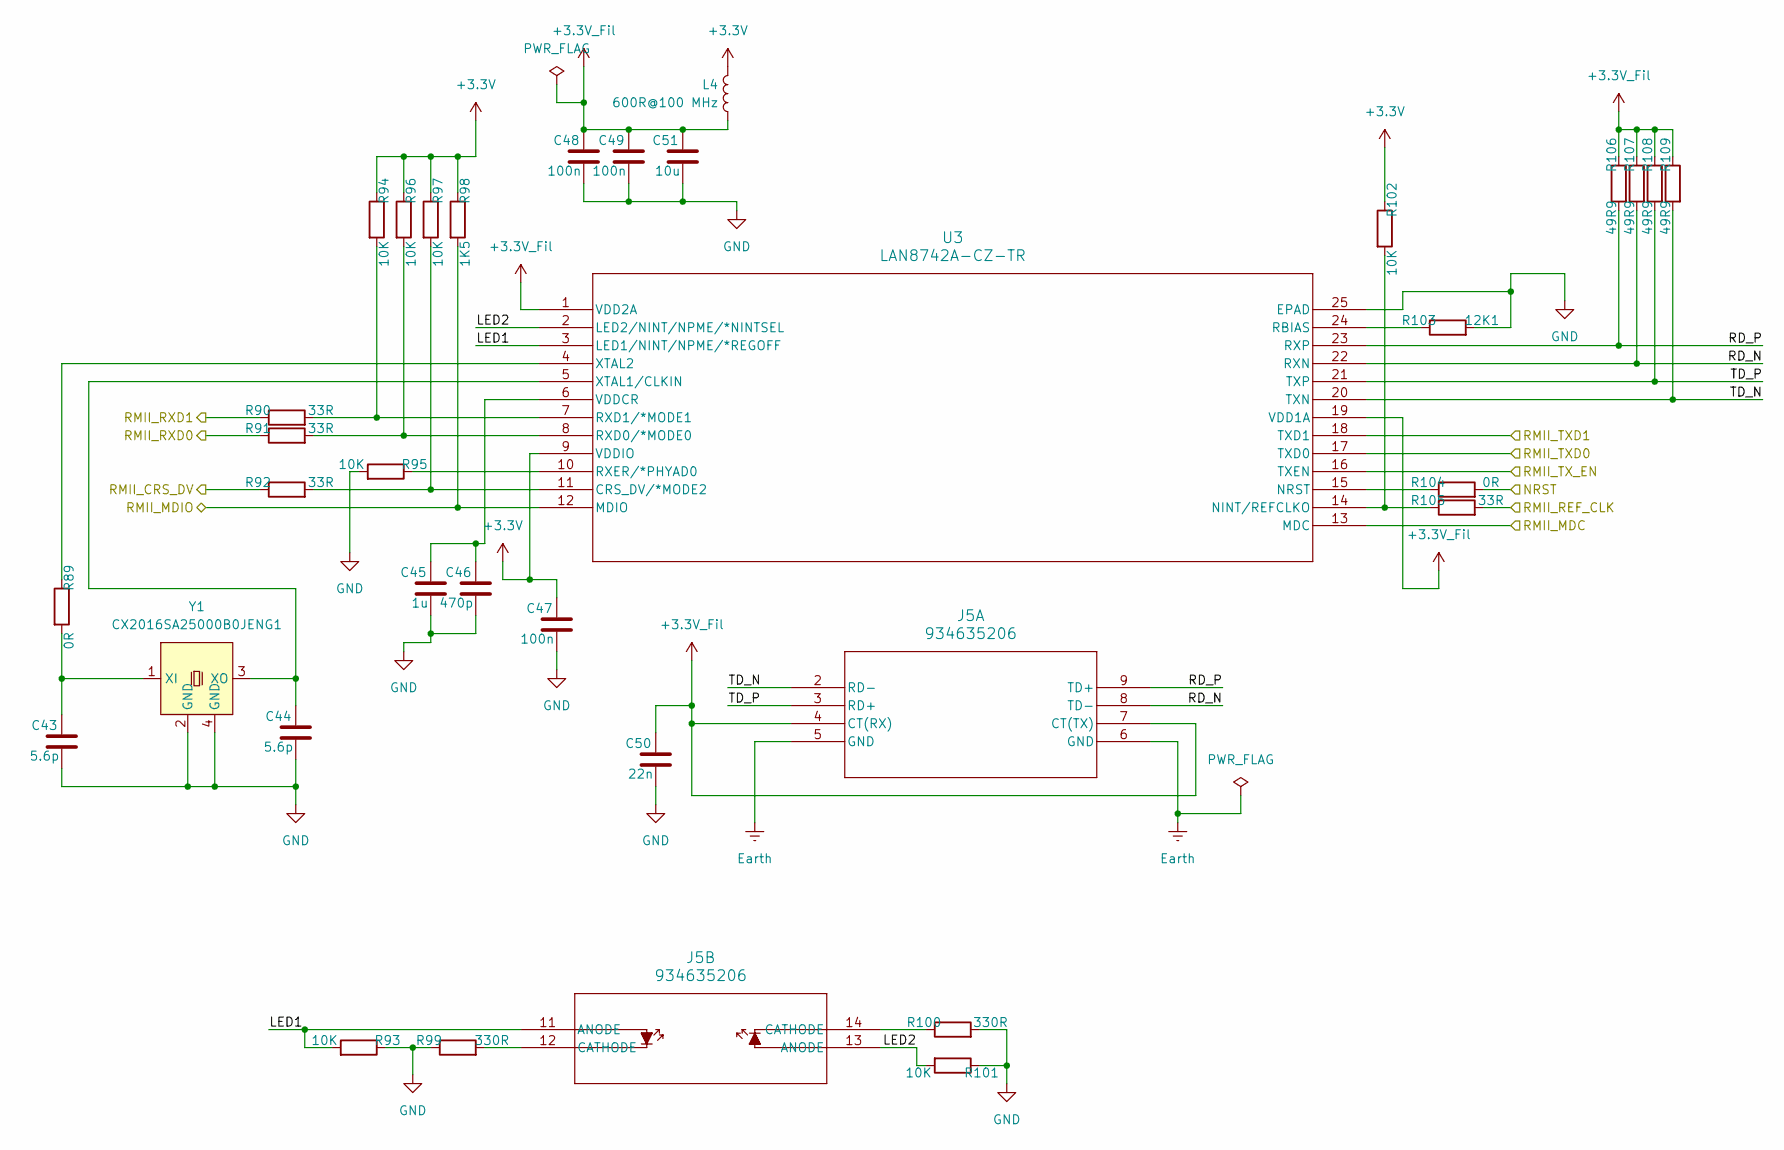
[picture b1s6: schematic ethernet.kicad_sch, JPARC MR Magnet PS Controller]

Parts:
C43, C44: 5.6p; C_0603_1608Metric
C45: 1u; C_0603_1608Metric
C46: 470p; C_0603_1608Metric
C47, C48, C49: 100n; C_0402_1005Metric
C50: 22n; C_0603_1608Metric
C51: 10u; C_0603_1608Metric
J5: 934635206; Molex_934635206_Shield_Lands
L4: 600R@100 MHz; L_0603_1608Metric
R89, R104: 0R; R_0603_1608Metric
R90, R91, R92, R105: 33R; R_0402_1005Metric
R93, R94, R95, R96, R97, R101, R102: 10K; R_0603_1608Metric
R98: 1K5; R_0603_1608Metric
R99, R100: 330R; R_0603_1608Metric
R103: 12K1; R_0603_1608Metric
R106, R107, R108, R109: 49R9; R_0603_1608Metric
U3: LAN8742A-CZ-TR; LAN8742A_QFN24_4x4_Tented_GND
Y1: CX2016SA25000B0JENG1; CX2016SA_2.0x1.6mm

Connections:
+3.3V: C47.1, L4.1, R94.1, R96.1, R97.1, R98.1, R102.1, U3.9 (VDDIO); also elsewhere on the board
+3.3V_Fil: C48.1, C49.1, C50.1, C51.1, J5.4 (CT(RX)), J5.7 (CT(TX)), L4.2, R106.1, R107.1, R108.1, R109.1, U3.1 (VDD2A), U3.19 (VDD1A)
/Ethernet Sheet/LED1: J5.11 (ANODE), R93.2, U3.3 (LED1/NINT/NPME/*REGOFF)
/Ethernet Sheet/LED2: J5.13 (ANODE), R101.2, U3.2 (LED2/NINT/NPME/*NINTSEL)
/Ethernet Sheet/RD_N: J5.8 (TD-), R107.2, U3.22 (RXN)
/Ethernet Sheet/RD_P: J5.9 (TD+), R106.2, U3.23 (RXP)
/Ethernet Sheet/TD_N: J5.2 (RD-), R109.2, U3.20 (TXN)
/Ethernet Sheet/TD_P: J5.3 (RD+), R108.2, U3.21 (TXP)
/STM32H7 Sheet/NRST: R104.2; also elsewhere on the board
/STM32H7 Sheet/PA1: R105.2; also elsewhere on the board
/STM32H7 Sheet/PA2: R98.2, U3.12 (MDIO); also elsewhere on the board
/STM32H7 Sheet/PA7: R92.1; also elsewhere on the board
/STM32H7 Sheet/PB13: U3.18 (TXD1); also elsewhere on the board
/STM32H7 Sheet/PC1: U3.13 (MDC); also elsewhere on the board
/STM32H7 Sheet/PC4: R91.1; also elsewhere on the board
/STM32H7 Sheet/PC5: R90.1; also elsewhere on the board
/STM32H7 Sheet/PG11: U3.16 (TXEN); also elsewhere on the board
/STM32H7 Sheet/PG13: U3.17 (TXD0); also elsewhere on the board
Earth: J5.5 (GND), J5.6 (GND)
GND: C43.2, C44.2, C45.2, C46.2, C47.2, C48.2, C49.2, C50.2, C51.2, R93.1, R95.2, R99.1, R100.2, R101.1, R103.2, U3.25 (EPAD), Y1.2 (GND), Y1.4 (GND); also elsewhere on the board
unnamed: J5.12 (CATHODE), R99.2
unnamed: J5.14 (CATHODE), R100.1
unnamed: R92.2, R97.2, U3.11 (CRS_DV/*MODE2)
unnamed: R102.2, R105.1, U3.14 (NINT/REFCLKO)
unnamed: R104.1, U3.15 (NRST)
unnamed: R103.1, U3.24 (RBIAS)
unnamed: R91.2, R96.2, U3.8 (RXD0/*MODE0)
unnamed: R90.2, R94.2, U3.7 (RXD1/*MODE1)
unnamed: R95.1, U3.10 (RXER/*PHYAD0)
unnamed: C45.1, C46.1, U3.6 (VDDCR)
unnamed: C44.1, U3.5 (XTAL1/CLKIN), Y1.3 (XO)
unnamed: R89.1, U3.4 (XTAL2)
unnamed: C43.1, R89.2, Y1.1 (XI)
